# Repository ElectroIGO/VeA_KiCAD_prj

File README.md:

# VeA_KiCAD_prj
Paredzēts kursa darba projektiem.

Made in LATVIA, by brand IGOTERU.

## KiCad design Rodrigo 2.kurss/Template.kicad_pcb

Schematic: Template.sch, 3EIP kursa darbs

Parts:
C1, C3, C4, C5, C8, C15: 100nF; C_0603_1608Metric_Pad1.05x0.95mm_HandSolder
C2: 220uF; CP_Elec_6.3x5.9
C6, C7, C9, C10, C11, C12, C13, C14: 1uF; C_0603_1608Metric_Pad1.05x0.95mm_HandSolder
C16: 47uF; CP_Elec_4x5.8
C17, C18: 220nF; C_0603_1608Metric_Pad1.05x0.95mm_HandSolder
CLK1: CLK; PinHeader_1x01_P2.00mm_Vertical
D1, D2, D5, D6: RB522ES; D_0201_0603Metric
D3, D4: RED; LED_1210_3225Metric_Pad1.42x2.65mm_HandSolder
GND1: GND; PinHeader_1x01_P2.00mm_Vertical
J1: 02x12; SAMTEC-SSW-112-02-X-D-RA
J2: Outside_Sensors; PinHeader_1x09_P1.27mm_Vertical
LOAD1: LOAD1; PinHeader_1x01_P2.00mm_Vertical
LOAD2: LOAD2; PinHeader_1x01_P2.00mm_Vertical
MISO1: MISO; PinHeader_1x01_P2.00mm_Vertical
MOSI1: MOSI; PinHeader_1x01_P2.00mm_Vertical
Q1, Q2: BSP250; SOT-223-3_TabPin2
Q3, Q5, Q6: BC817; SOT-23
Q4: MMBT3906; SOT-23
R1, R3: 0R1; R_0603_1608Metric_Pad1.05x0.95mm_HandSolder
R2, R4: 1k; R_0603_1608Metric_Pad1.05x0.95mm_HandSolder
R5, R6, R28, R29: 82k; R_0603_1608Metric_Pad1.05x0.95mm_HandSolder
R7, R8, R9, R10, R15, R16, R17, R18, R19, R24, R27, R30, R31, R32: 12k; R_0603_1608Metric_Pad1.05x0.95mm_HandSolder
R20, R21: 470; R_0603_1608Metric_Pad1.05x0.95mm_HandSolder
R22, R23: 12K; R_0603_1608Metric_Pad1.05x0.95mm_HandSolder
R25: 220k; R_0603_1608Metric_Pad1.05x0.95mm_HandSolder
R26: 470k; R_0603_1608Metric_Pad1.05x0.95mm_HandSolder
U1, U4: LM358; SOIC-8_5.23x5.23mm_P1.27mm
U2: SN74CBTLV3251PW; SSOP-16_4.4x5.2mm_P0.65mm
U3, U8: BME280
U5: 4013; SSOP-14_5.3x6.2mm_P0.65mm
U6, U7: MPU9250
U9: 4017; SOIC-16_3.9x9.9mm_P1.27mm

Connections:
3.3V: C2.1, C4.1, C5.1, J1.3, Q1.3 (S), Q2.3 (S), Q4.2 (E), R7.1, R9.1, R18.1, R19.1, R23.1, R25.1, R27.1, R28.1, R29.1, R30.1, U1.8 (V+), U2.16 (VCC), U4.8 (V+), U5.14 (VDD), U9.16 (VDD)
CLK: CLK1.1, J1.20, J2.5, U3.4 (SCK), U6.23, U7.23, U8.4 (SCK)
CS1: U2.4 (B1), U3.2 (CSB)
CS2: U2.3 (B2), U7.22
CS3: J2.2, U2.2 (B3)
CS5: U2.15 (B5), U8.2 (CSB)
CS6: U2.14 (B6), U6.22
CS7: J2.8, U2.13 (B7)
GND: C2.2, C4.2, C5.2, C16.2, GND1.1, J1.1, J1.12, Q3.2 (E), Q5.2 (E), Q6.2 (E), R1.2, R2.1, R3.2, R4.1, R8.2, R10.2, R15.2, R16.1, R17.2, R20.2, R21.2, R24.2, R26.2, R31.2, R32.2, U1.4 (V-), U2.7 (OE), U2.8 (GND), U4.4 (V-), U5.6 (S), U5.7 (VSS), U5.8 (S), U9.8 (VSS); also elsewhere on the board
GNDS1: C1.2, C3.2, C7.2, C10.2, C13.1, C14.1, J2.6, R3.1, U3.1 (GND), U3.7 (GND), U4.5 (+), U7.11, U7.18, U7.20
LOAD1: C1.1, C3.1, C7.1, C13.2, C14.2, J2.1, LOAD1.1, Q2.2 (D), U3.6 (VDDIO), U3.8 (VDD), U7.1, U7.8, U7.13
LOAD2: C6.1, C8.1, C11.2, C12.2, C15.1, J2.9, LOAD2.1, Q1.2 (D), U6.1, U6.8, U6.13, U8.6 (VDDIO), U8.8 (VDD)
MISO: J1.18, J2.3, MISO1.1, U3.5 (SDO), U6.9, U7.9, U8.5 (SDO)
MOSI: J1.19, J2.4, MOSI1.1, U3.3 (SDI), U6.24, U7.24, U8.3 (SDI)
MUX_ADDR1: J1.21, U2.11 (S0)
MUX_ADDR2: J1.22, U2.10 (S1)
MUX_ADDR3: J1.23, U2.9 (S2)
MUX_DATA: J1.24, U2.5 (A)
unnamed: C9.1, U6.10
unnamed: C10.1, U7.10
unnamed: C16.1, Q3.1 (B), R25.2, R26.1
unnamed: C17.1, Q6.1 (B), R28.2
unnamed: C17.2, Q5.3 (C), R27.2, U9.14 (CLK)
unnamed: C18.1, Q6.3 (C), R30.2
unnamed: C18.2, Q5.1 (B), R29.2
unnamed: D1.1 (K), D2.1 (K), R15.1, U5.3 (C)
unnamed: D1.2 (A), U1.1
unnamed: D2.2 (A), U4.1, U5.11 (C)
unnamed: D3.1 (K), R20.1
unnamed: D3.2 (A), Q1.1 (G), R18.2, R32.1, U5.2 (~Q), U5.5 (D)
unnamed: D4.1 (K), R21.1
unnamed: D4.2 (A), Q2.1 (G), R19.2, U5.13 (Q)
unnamed: D5.1 (K), D6.1 (K), U9.15 (Reset)
unnamed: D6.2 (A), Q4.3 (C), R24.1, U9.13 (CKEN)
unnamed: Q3.3 (C), R22.1
unnamed: Q4.1 (B), R22.2, R23.2
unnamed: R2.2, R5.1, U1.6 (-)
unnamed: R4.2, R6.1, U4.6 (-)
unnamed: R5.2, U1.2 (-), U1.7
unnamed: R6.2, U4.2 (-), U4.7
unnamed: R7.2, R8.1, U1.3 (+)
unnamed: R9.2, R10.1, U4.3 (+)
unnamed: R31.1, U5.9 (D), U5.12 (~Q)
Reset: D5.2 (A), R16.2, R17.1, U5.4 (R), U5.10 (R), U9.1 (Q5)

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
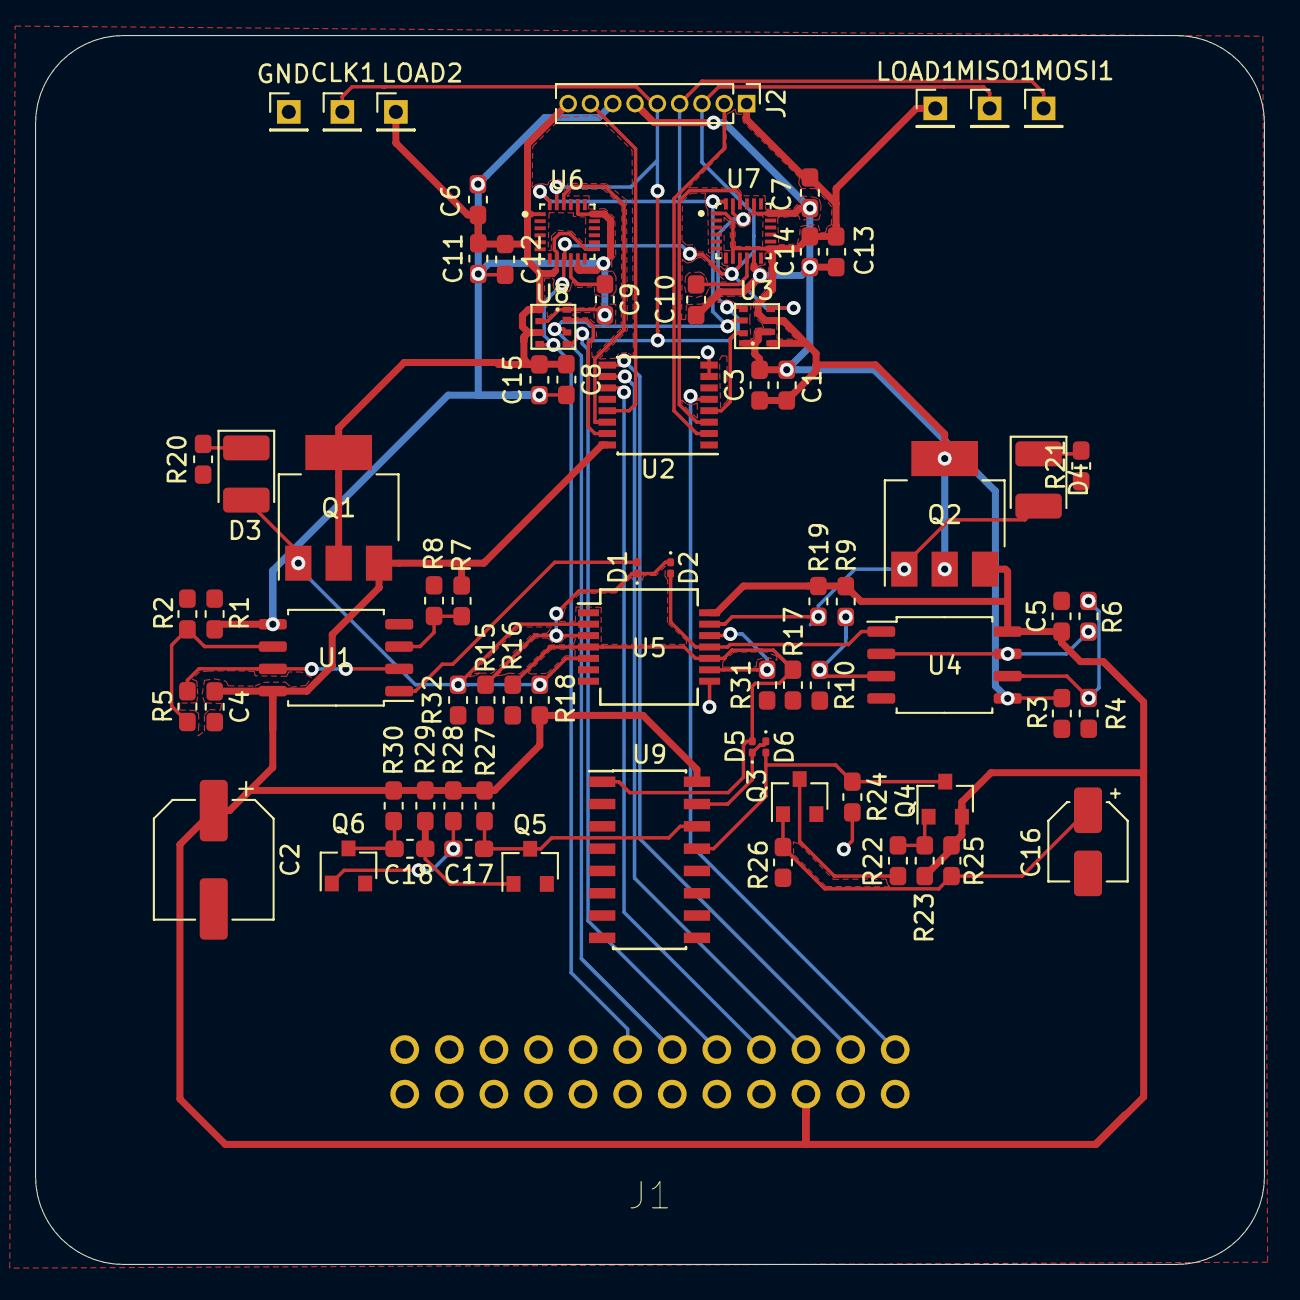
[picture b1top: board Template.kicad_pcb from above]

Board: 2 copper layers, 70.0 x 70.0 mm, 75 parts (0 on the bottom side), 45 nets.

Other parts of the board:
GND: GND; PinHeader_1x01_P2.00mm_Vertical

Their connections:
GND: GND.1; also elsewhere on the board

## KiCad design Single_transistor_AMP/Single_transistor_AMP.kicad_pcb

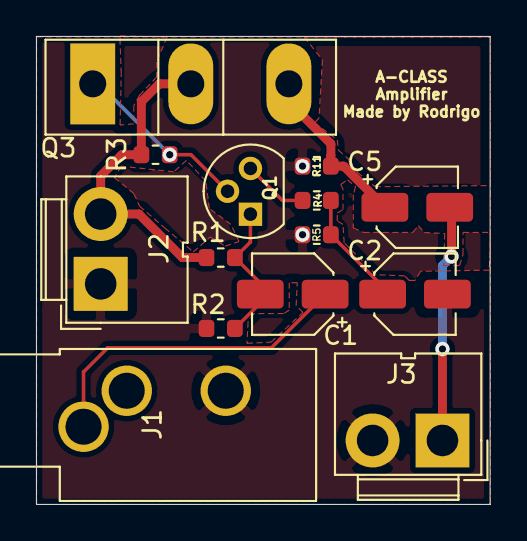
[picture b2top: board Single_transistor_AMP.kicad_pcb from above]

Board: 2 copper layers, 25.2 x 26.0 mm, 14 parts (0 on the bottom side), 9 nets.

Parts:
C1: 10uF; CP_Elec_4x4.5
C2, C5: 470uF; CP_Elec_4x4.5
J1: AudioJack2_Ground; Jack_3.5mm_CUI_SJ1-3533NG_Horizontal_CircularHoles
J2: 32V; JWT_A3963_1x02_P3.96mm_Vertical
J3: Signal out; JWT_A3963_1x02_P3.96mm_Vertical
Q1: BC546; TO-92
Q3: TIP140; TO-247-3_Vertical
R1: 110k; R_0603_1608Metric
R2: 6k8; R_0603_1608Metric
R3: 3k; R_0603_1608Metric
R4, R5: 100; R_0603_1608Metric
R11: 16; R_0603_1608Metric

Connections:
GND: C2.2, J1.R, J2.1, J3.2, R2.2, R5.2, R11.2
unnamed: C1.1, J1.S
unnamed: C1.2, Q1.1, R1.2, R2.1
unnamed: C2.1, R4.2, R5.1
unnamed: C5.1, Q3.3, R11.1
unnamed: C5.2, J3.1
unnamed: J2.2, Q3.2, R1.1, R3.1
unnamed: Q1.2, Q3.1, R3.2
unnamed: Q1.3, R4.1

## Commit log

2020-09-22 README failā tika veiktas izmaiņas
2020-10-06 Iesniegts otrais MD
2020-10-13 Trešais MD
2020-10-19 Trīspakāpju pastiprinātājs/Pārtesteets
2020-10-22 Treniņuzdevums 'Battery Holder
2020-10-23 Batteriju izklājlaukumu mājasdarbs
2020-11-02 Treniņuzdevumi
2020-11-18 Izpildīts 8 lekcijas MD
2020-12-02 8 nodarbības MD
2020-12-02 9. nodarbības MD
2020-12-09 10 MD
2021-01-25 Kursa darbs
